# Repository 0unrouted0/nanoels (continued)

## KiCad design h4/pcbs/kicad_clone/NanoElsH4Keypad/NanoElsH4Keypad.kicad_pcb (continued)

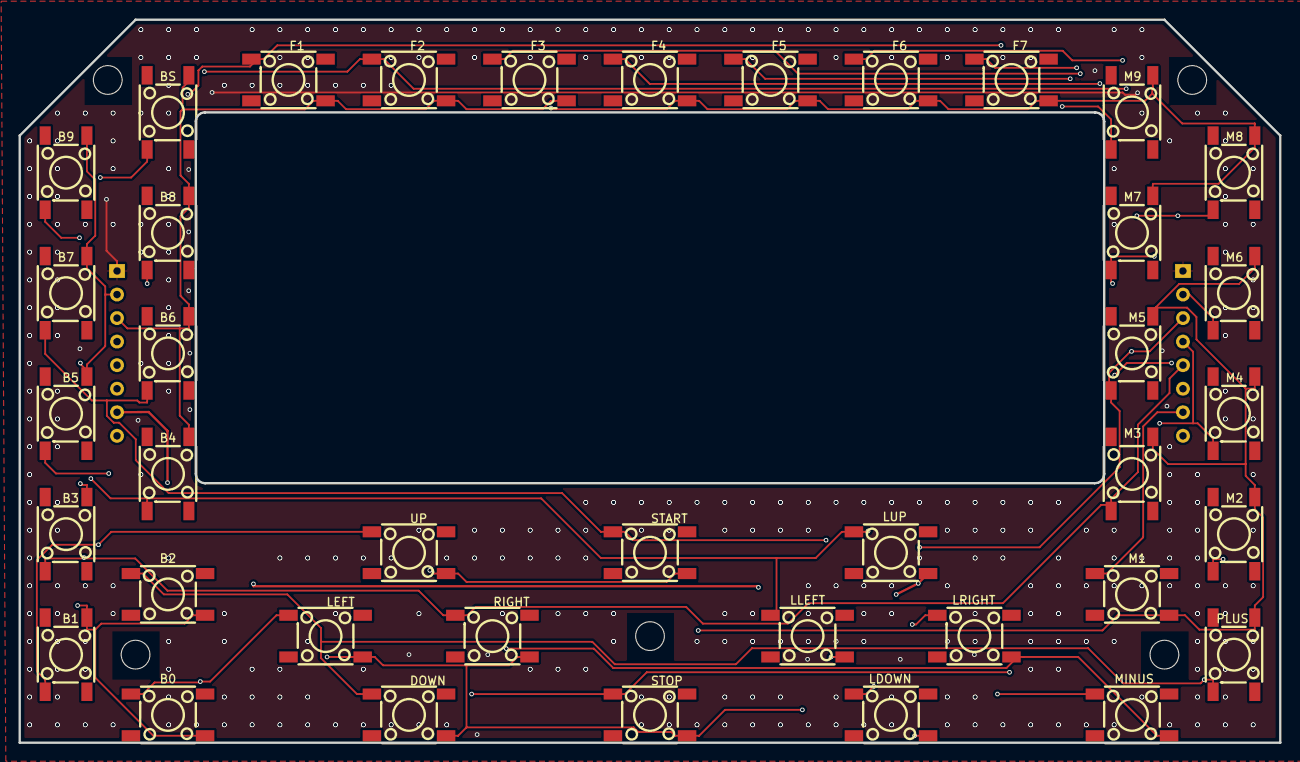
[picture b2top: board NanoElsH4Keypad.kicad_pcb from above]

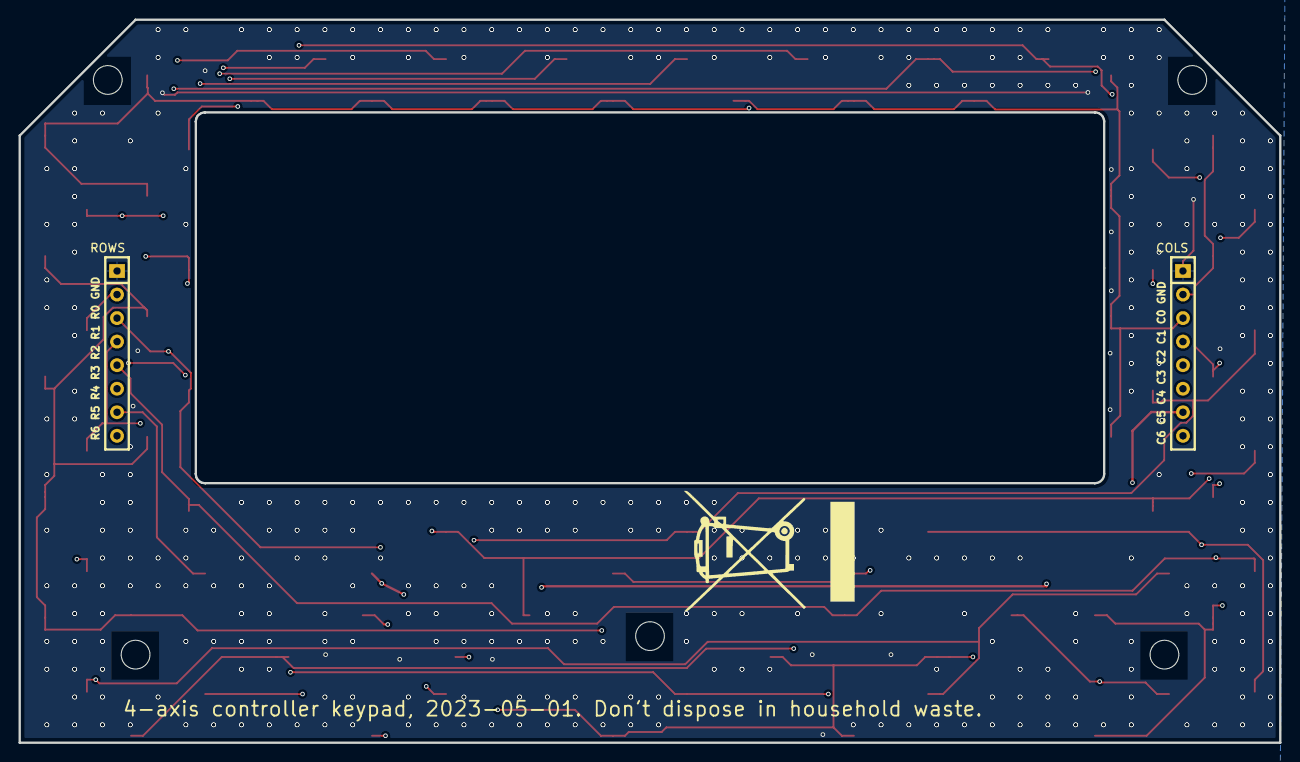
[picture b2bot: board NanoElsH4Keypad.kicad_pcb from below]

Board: 4 copper layers, 136.0 x 78.0 mm, 46 parts (2 on the bottom side), 15 nets.

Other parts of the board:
Hole_gge12452: Hole_gge12452
Hole_gge12497: Hole_gge12497
Hole_gge12557: Hole_gge12557
Hole_gge12572: Hole_gge12572
Hole_gge12587: Hole_gge12587

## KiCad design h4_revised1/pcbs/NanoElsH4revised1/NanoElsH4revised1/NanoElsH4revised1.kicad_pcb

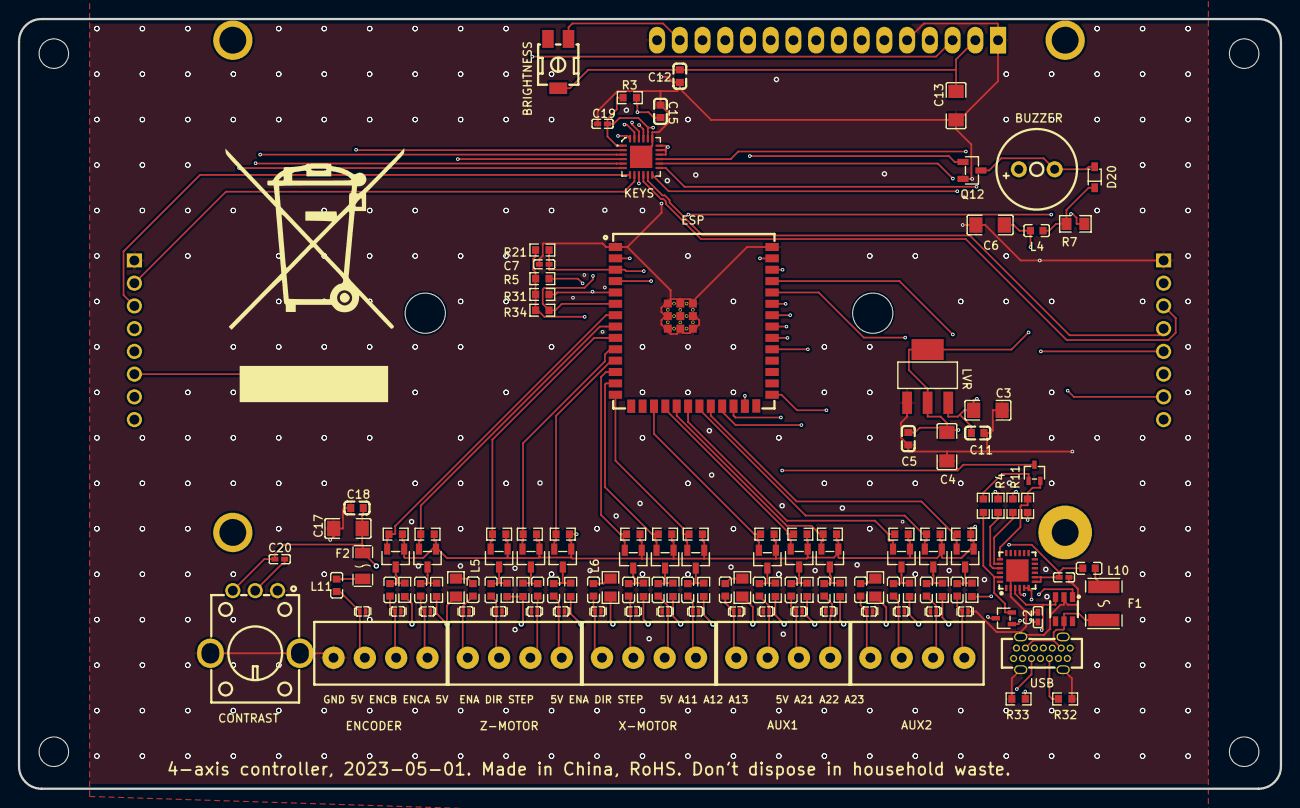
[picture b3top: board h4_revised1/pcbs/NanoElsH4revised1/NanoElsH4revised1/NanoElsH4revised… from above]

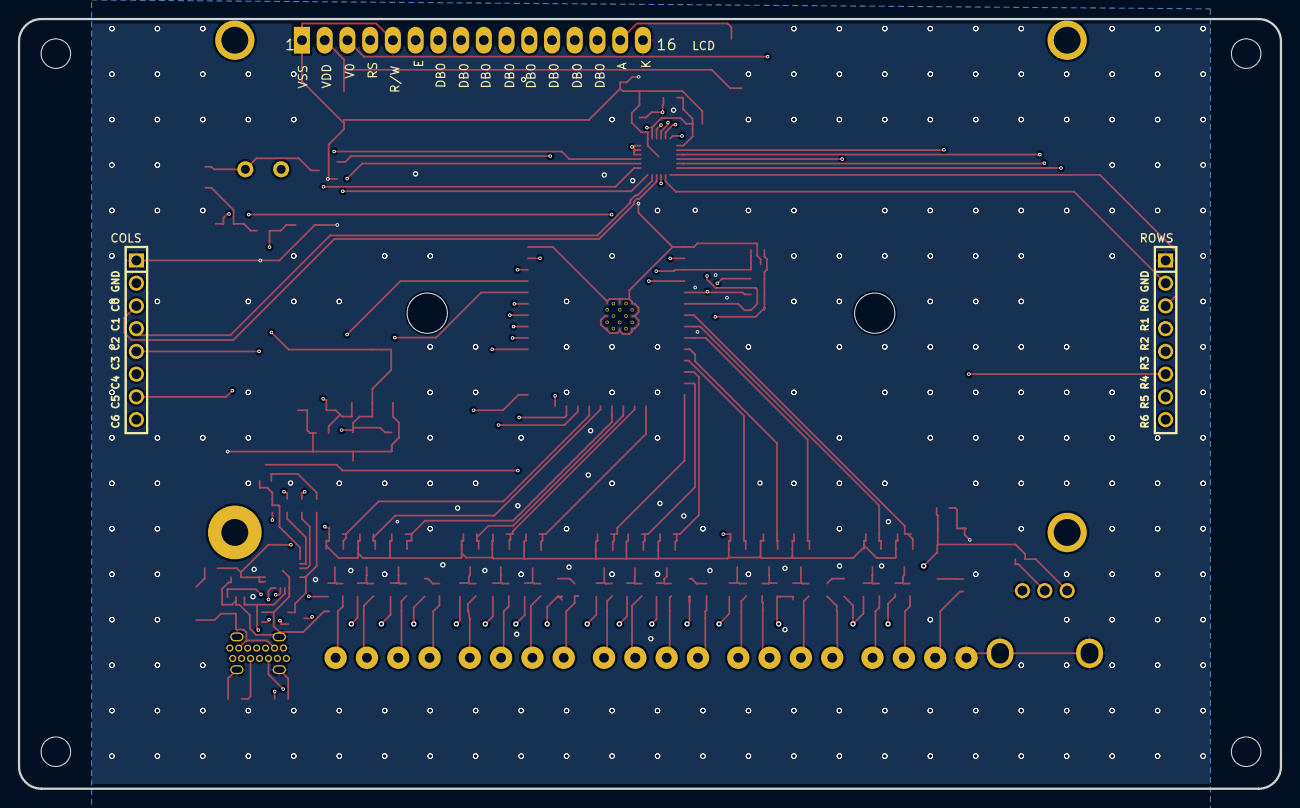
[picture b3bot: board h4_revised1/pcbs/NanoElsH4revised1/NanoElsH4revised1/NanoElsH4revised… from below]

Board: 4 copper layers, 141.0 x 86.0 mm, 142 parts (3 on the bottom side), 106 nets.

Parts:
AUX1, AUX2: DB2EVC-3.5-4P-GN; CONN-TH_4P-P3.50_DB2EVC-3.5-4P-GN
BRIGHTNESS: 1k; RES-ADJ-SMD_3P-L4.5-W4.5-P2.30-LS6.2-BL-FS
BUZZER: QMB-09B-03; BUZ-TH_BD9.0-P4.00-D0.6-FD
C1, C2, C7: 1uF; C0402
C3, C4, C6, C13, C17: 10uF; C1206
C5, C11, C12, C15, C18: 100nF; C0603
C19, C20: 1nF; C0402
COLS: MF254V-11-08-0540; HDR-TH_8P-P2.54-V-F-3
CONTRAST: 10kΩ; RES-TH_RK09K113004U
D20: 1N4148WS T4; SOD-323_L1.8-W1.3-LS2.5-RD
D21, D22, D23, D24, D25, D26, D27, D28, D29, D30, D31, D32, D33, D34, D35, D36, D37, D38, D39: KESD9B5VL; X1-DFN1006-2_L1.0-W0.6-P0.65-BI
ENCODER: DB2EVC-3.5-4P-GN; CONN-TH_4P-P3.50_DB2EVC-3.5-4P-GN
ESP: ESP32-S3-WROOM-1U-N16R2; WIRELM-SMD_ESP32-S3-WROOM-1U
F1: SMD1812P030TF; F1812
F2: nSMD010; F1206
Hole_gge813785: Hole_gge813785
Hole_gge813800: Hole_gge813800
Hole_gge6227889318616504: Hole_gge6227889318616504
Hole_gge6227889318616534: Hole_gge6227889318616534
Hole_gge6227889318616549: Hole_gge6227889318616549
Hole_gge6227889318616564: Hole_gge6227889318616564
KEYS: TCA8418RTWR; WQFN-24_L4.0-W4.0-P0.50-TL-EP2.5
L1, L2, L3, L4, L5, L6, L10, L11, L22, L23, L24, L25, L26, L27, L28, L29, L31, L32, L33, L34, L36: 120Ω; L0603
LCD: LCD2004; LCD2004-PHT
LVR: AMS1117-3.3; SOT-223-3_L6.4-W3.5-P2.30-LS7.0-BR
Q1, Q2, Q5, Q6, Q7, Q8, Q9, Q10, Q11, Q12, Q13, Q14, Q15, Q16, Q18: SI2302ADS-T1; SOT-23-3_L2.9-W1.3-P1.90-LS2.4-BR
Q3, Q4: S9013W; SOT-323-3_L2.0-W1.3-P1.30-LS2.1-BR
R1, R2, R6, R15, R17, R18, R19, R20, R22, R23, R24, R25, R26, R27, R28, R29, R30, R35, R38, R39, R40, R41, R42, R43, R44, R45, R48, R49: 2kΩ; R0603
R3, R5, R21, R31, R32, R33, R34: 5.1kΩ; R0603
R4, R11: 470Ω; R0603
R7: 100Ω; R0805
R12, R16, R36, R37: 200Ω; R0805
R13, R14: 10kΩ; R0603
ROWS: MF254V-11-08-0540; HDR-TH_8P-P2.54-V-F-3
TV1: SRV05-4-P-T7; SOT-23-6_L2.9-W1.6-P0.95-LS2.8-BR
USB: 918-468K2029E50000; USB-C-TH_918-468K2029E50000
USB2UART: CH9102F; QFN-24_L4.0-W4.0-P0.50-BL-EP2.5
X-MOTOR: DB2EVC-3.5-4P-GN; CONN-TH_4P-P3.50_DB2EVC-3.5-4P-GN
Z-MOTOR: DB2EVC-3.5-4P-GN; CONN-TH_4P-P3.50_DB2EVC-3.5-4P-GN

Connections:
3V: C4.2, C5.1, C6.2, C15.1, ESP.2, KEYS.21, L4.1, LVR.2, LVR.4, Q1.1, Q2.1, Q5.1, Q6.1, Q7.1, Q8.1, Q9.1, Q10.1, Q11.1, Q13.1, Q14.1, Q15.1, Q16.1, Q18.1, R1.2, R3.1, R5.1, R15.2, R18.2, R19.2, R21.1, R22.2, R24.2, R27.2, R28.2, R30.2, R31.1, R34.1, R39.2, R41.2, R42.2, R44.2, R48.2
5V: BRIGHTNESS.2, C1.2, C3.2, C11.2, C12.2, C13.2, C17.2, C18.2, C20.1, CONTRAST.3, F2.1, L10.2, LCD.2, LVR.3, R2.1, R6.1, R12.1, R16.1, R17.1, R20.1, R23.1, R25.1, R26.1, R29.1, R35.1, R36.1, R37.1, R38.1, R40.1, R43.1, R45.1, R49.1, USB2UART.7, USB2UART.8
AUX1_4: AUX1.4, D24.1, L2.2
AUX2_4: AUX2.4, D25.1, L3.2
AUX11-3V: ESP.17, Q9.2, R27.1
AUX11-5V: AUX1.3, D36.2, L27.1
AUX12-3V: ESP.18, Q14.2, R41.1
AUX12-5V: AUX1.2, D35.2, L32.1
AUX13-3V: ESP.19, Q13.2, R39.1
AUX13-5V: AUX1.1, D34.2, L31.1
AUX21-3V: ESP.20, Q18.2, R48.1
AUX21-5V: AUX2.3, D39.2, L36.1
AUX22-3V: ESP.21, Q15.2, R42.1
AUX22-5V: AUX2.2, D38.1, L33.1
AUX23-3V: ESP.22, Q16.2, R44.1
AUX23-5V: AUX2.1, D37.2, L34.1
BOOT: ESP.27, Q3.3
BUZZ: ESP.4, Q12.1
BUZZER_1: BUZZER.1, R7.2
BUZZER_2: BUZZER.2, D20.2, Q12.3
COL0: COLS.2, KEYS.9
COL1: COLS.3, KEYS.10
COL2: COLS.4, KEYS.11
COL3: COLS.5, KEYS.12
COL4: COLS.6, KEYS.13
COL5: COLS.7, KEYS.14
COL6: COLS.8, KEYS.15
DMINUS: TV1.1, USB.A7, USB.B7, USB2UART.4
DPLUS: TV1.3, USB.A6, USB.B6, USB2UART.3
EN: C7.1, ESP.3, Q4.3, R21.2
ENCA-3V: ESP.8, Q11.2, R30.1
ENCA-5V: D32.2, ENCODER.1, L29.1
ENCB-3V: ESP.7, Q10.2, R28.1
ENCB-5V: D33.2, ENCODER.2, L28.1
F1_2: F1.2, L10.1
F2_2: F2.2, L11.1
GND: C1.1, C2.2, C3.1, C4.1, C5.2, C6.1, C7.2, C11.1, C12.1, C13.1, C15.2, C17.1, C18.1, C19.1, COLS.1, CONTRAST.1, CONTRAST.4, CONTRAST.5, D21.1, D22.1, D23.2, D24.2, D25.2, D26.1, D27.1, D28.1, D29.1, D30.1, D31.1, D32.1, D33.1, D34.1, D35.1, D36.1, D37.1, D38.2, D39.1, ENCODER.4, ESP.1, ESP.40, ESP.41, KEYS.19, KEYS.25, LCD.1, LCD.5, LCD.16, LVR.1, Q12.2, R32.2, R33.1, ROWS.1, TV1.2, USB.15, USB.16, USB.17, USB.18, USB.A1, USB.A12, USB.B1, USB.B12, USB2UART.2, USB2UART.25
INT: KEYS.24, R5.2
KEYS_1: C19.2, KEYS.1, KEYS.16, KEYS.17, KEYS.18, KEYS.20, R3.2
L1_2: L1.2, Q1.3, R2.2
L2_1: L2.1, R36.2
L3_1: L3.1, R37.2
L5_1: L5.1, R16.2
L5_2: D22.2, L5.2, Z-MOTOR.4
L6_1: L6.1, R12.2
L6_2: D23.1, L6.2, X-MOTOR.4
L11_2: D21.2, ENCODER.3, L11.2
L22_2: L22.2, Q2.3, R6.2
L23_2: L23.2, Q5.3, R17.2
L27_2: L27.2, Q9.3, R26.2
L31_2: L31.2, Q13.3, R38.2
L32_2: L32.2, Q14.3, R40.2
LCD-D0: ESP.24, LCD.7
LCD-D1: ESP.31, LCD.8
LCD-D2: ESP.32, LCD.9
LCD-D3: ESP.33, LCD.10
LCD-D4: ESP.34, LCD.11
LCD-D5: ESP.35, LCD.12
LCD-D6: ESP.38, LCD.13
LCD-D7: ESP.39, LCD.14
LCD-EN: ESP.25, LCD.6
LCD-RS: ESP.23, LCD.4
LCD_3: C20.2, CONTRAST.2, LCD.3
LCD_15: BRIGHTNESS.3, LCD.15
Q3_1: Q3.1, R13.2
Q4_1: Q4.1, R14.2
Q6_3: L24.2, Q6.3, R20.2
Q7_3: L25.2, Q7.3, R23.2
Q8_3: L26.2, Q8.3, R25.2
Q10_3: L28.2, Q10.3, R29.2
Q11_3: L29.2, Q11.3, R35.2
Q15_3: L33.2, Q15.3, R43.2
Q16_3: L34.2, Q16.3, R45.2
Q18_3: L36.2, Q18.3, R49.2
R7_1: D20.1, L4.2, R7.1
ROW0: KEYS.8, ROWS.2
ROW1: KEYS.7, ROWS.3
ROW2: KEYS.6, ROWS.4
ROW3: KEYS.5, ROWS.5
ROW4: KEYS.4, ROWS.6
ROW5: KEYS.3, ROWS.7
ROW6: KEYS.2, ROWS.8
RX: ESP.36, R4.2
SCL: ESP.5, KEYS.23, R31.2
SDA: ESP.6, KEYS.22, R34.2
TX: ESP.37, R11.2
USB2UART_5: C2.1, USB2UART.5, USB2UART.6
USB2UART_19: Q4.2, R13.1, USB2UART.19
USB2UART_20: R11.1, USB2UART.20
USB2UART_21: R4.1, USB2UART.21
USB2UART_23: Q3.2, R14.1, USB2UART.23
USB_A5: R33.2, USB.A5
USB_B5: R32.1, USB.B5
VBUS: F1.1, TV1.5, USB.A4, USB.A9, USB.B4, USB.B9
XDIR-3V: ESP.13, Q7.2, R22.1
XDIR-5V: D30.2, L25.1, X-MOTOR.2
XENA-3V: ESP.12, Q6.2, R19.1
XENA-5V: D31.2, L24.1, X-MOTOR.3
XSTEP-3V: ESP.14, Q8.2, R24.1
XSTEP-5V: D29.2, L26.1, X-MOTOR.1
ZDIR-3V: ESP.10, Q2.2, R15.1
ZDIR-5V: D27.2, L22.1, Z-MOTOR.2
ZENA-3V: ESP.9, Q5.2, R18.1
ZENA-5V: D28.2, L23.1, Z-MOTOR.3
ZSTEP-3V: ESP.11, Q1.2, R1.1
ZSTEP-5V: D26.2, L1.1, Z-MOTOR.1

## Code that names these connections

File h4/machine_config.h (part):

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#define ENC_A 7
#define ENC_B 15

#define BUZZ 4 // Buzzer
#define SCL 5  // I2C clock, to the keypad controller
#define SDA 6  // I2C data

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#define A23 14

// Character LCD in 8-bit parallel mode: rs, enable, then d0-d7.
#define LCD_RS 21
#define LCD_EN 48
#define LCD_D0 47
#define LCD_D1 38
#define LCD_D2 39
#define LCD_D3 40
#define LCD_D4 41
#define LCD_D5 42
#define LCD_D6 2
#define LCD_D7 1
#define LCD_COLUMNS 20
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
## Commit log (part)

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2024-05-05 - Added KiCad files
2024-05-05 - moved files
2024-06-24 - added base software
2024-06-24 update (ESP32 lib): Update of ESP32 component in Arduino Upgrade to Espressive ESP32 3.0.1 boards package (based on ESP-IDF v5.1.4). Therefore "pulse counter" and "hardware timer" rewritten.
    feat (display): Display in I2C mode
    Added possibility for display in I2C mode for displays with I2C backpack (e.g. PCF8574). Seems currently working faultless together with secondary I2C channel for keypad interface. Added LiquidCrysta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
    test: State of testing incomplete
    Currently not completely tested, but encoder detects something. Hardware timer for ASYNC and A1
2024-06-24 - Added actual KiCad 8 files (layout ready, but some cosmetic documentation ToDo's)
2024-06-24 doc: added comment
2025-04-05 - KiCad 9...
2025-04-05 - activated I2C display - Cahnged lathe parameters - Changed binary define prefix
2025-04-06 - Added suggested code for backslash and show limit values. (Discussion issue #301 and issue #242) - Tested backslash settings via dial gauge and after power reset. Seems to be OK, including the sett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
